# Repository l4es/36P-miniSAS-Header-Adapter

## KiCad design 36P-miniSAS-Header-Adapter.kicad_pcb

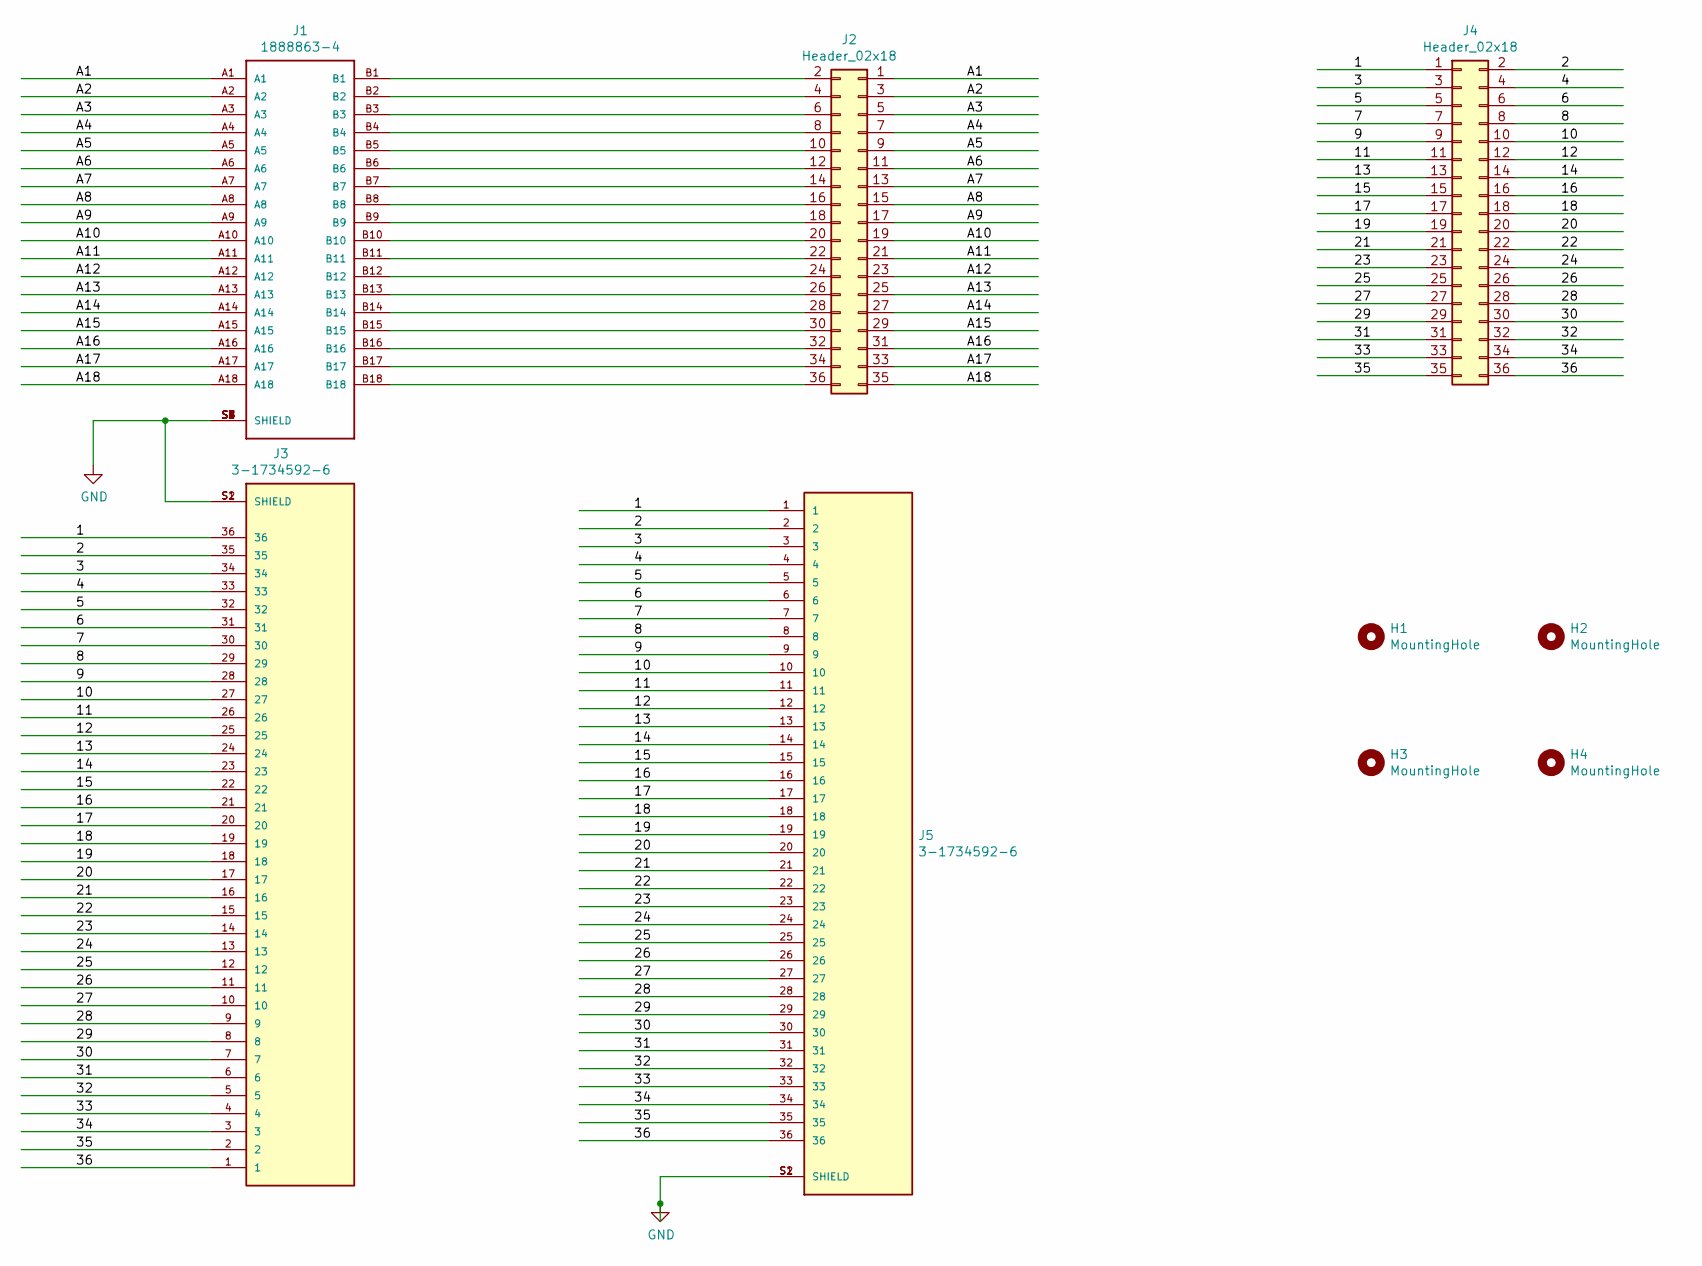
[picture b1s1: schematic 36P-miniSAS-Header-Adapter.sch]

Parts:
H1, H2, H3, H4: MountingHole; MountingHole_3.2mm_M3
J1: 1888863-4; TE_1888863-4
J2, J4: Header_02x18; PinHeader_2x18_P2.54mm_Vertical
J3, J5: 3-1734592-6; TE_3-1734592-6; PARTREV C

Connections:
/1: J3.36, J4.1, J5.1
/2: J3.35, J4.2, J5.2
/3: J3.34, J4.3, J5.3
/4: J3.33, J4.4, J5.4
/5: J3.32, J4.5, J5.5
/6: J3.31, J4.6, J5.6
/7: J3.30, J4.7, J5.7
/8: J3.29, J4.8, J5.8
/9: J3.28, J4.9, J5.9
/10: J3.27, J4.10, J5.10
/11: J3.26, J4.11, J5.11
/12: J3.25, J4.12, J5.12
/13: J3.24, J4.13, J5.13
/14: J3.23, J4.14, J5.14
/15: J3.22, J4.15, J5.15
/16: J3.21, J4.16, J5.16
/17: J3.20, J4.17, J5.17
/18: J3.19, J4.18, J5.18
/19: J3.18, J4.19, J5.19
/20: J3.17, J4.20, J5.20
/21: J3.16, J4.21, J5.21
/22: J3.15, J4.22, J5.22
/23: J3.14, J4.23, J5.23
/24: J3.13, J4.24, J5.24
/25: J3.12, J4.25, J5.25
/26: J3.11, J4.26, J5.26
/27: J3.10, J4.27, J5.27
/28: J3.9, J4.28, J5.28
/29: J3.8, J4.29, J5.29
/30: J3.7, J4.30, J5.30
/31: J3.6, J4.31, J5.31
/32: J3.5, J4.32, J5.32
/33: J3.4, J4.33, J5.33
/34: J3.3, J4.34, J5.34
/35: J3.2, J4.35, J5.35
/36: J3.1, J4.36, J5.36
/A1: J1.A1, J2.1
/A2: J1.A2, J2.3
/A3: J1.A3, J2.5
/A4: J1.A4, J2.7
/A5: J1.A5, J2.9
/A6: J1.A6, J2.11
/A7: J1.A7, J2.13
/A8: J1.A8, J2.15
/A9: J1.A9, J2.17
/A10: J1.A10, J2.19
/A11: J1.A11, J2.21
/A12: J1.A12, J2.23
/A13: J1.A13, J2.25
/A14: J1.A14, J2.27
/A15: J1.A15, J2.29
/A16: J1.A16, J2.31
/A17: J1.A17, J2.33
/A18: J1.A18, J2.35
GND: J1.S1 (SHIELD), J1.S2 (SHIELD), J1.S3 (SHIELD), J1.S4 (SHIELD), J1.S5 (SHIELD), J1.S6 (SHIELD), J1.S7 (SHIELD), J1.S8 (SHIELD), J3.S1 (SHIELD), J3.S2 (SHIELD), J5.S1 (SHIELD), J5.S2 (SHIELD)
unnamed: J1.B1, J2.2
unnamed: J1.B2, J2.4
unnamed: J1.B3, J2.6
unnamed: J1.B4, J2.8
unnamed: J1.B5, J2.10
unnamed: J1.B6, J2.12
unnamed: J1.B7, J2.14
unnamed: J1.B8, J2.16
unnamed: J1.B9, J2.18
unnamed: J1.B10, J2.20
unnamed: J1.B11, J2.22
unnamed: J1.B12, J2.24
unnamed: J1.B13, J2.26
unnamed: J1.B14, J2.28
unnamed: J1.B15, J2.30
unnamed: J1.B16, J2.32
unnamed: J1.B17, J2.34
unnamed: J1.B18, J2.36

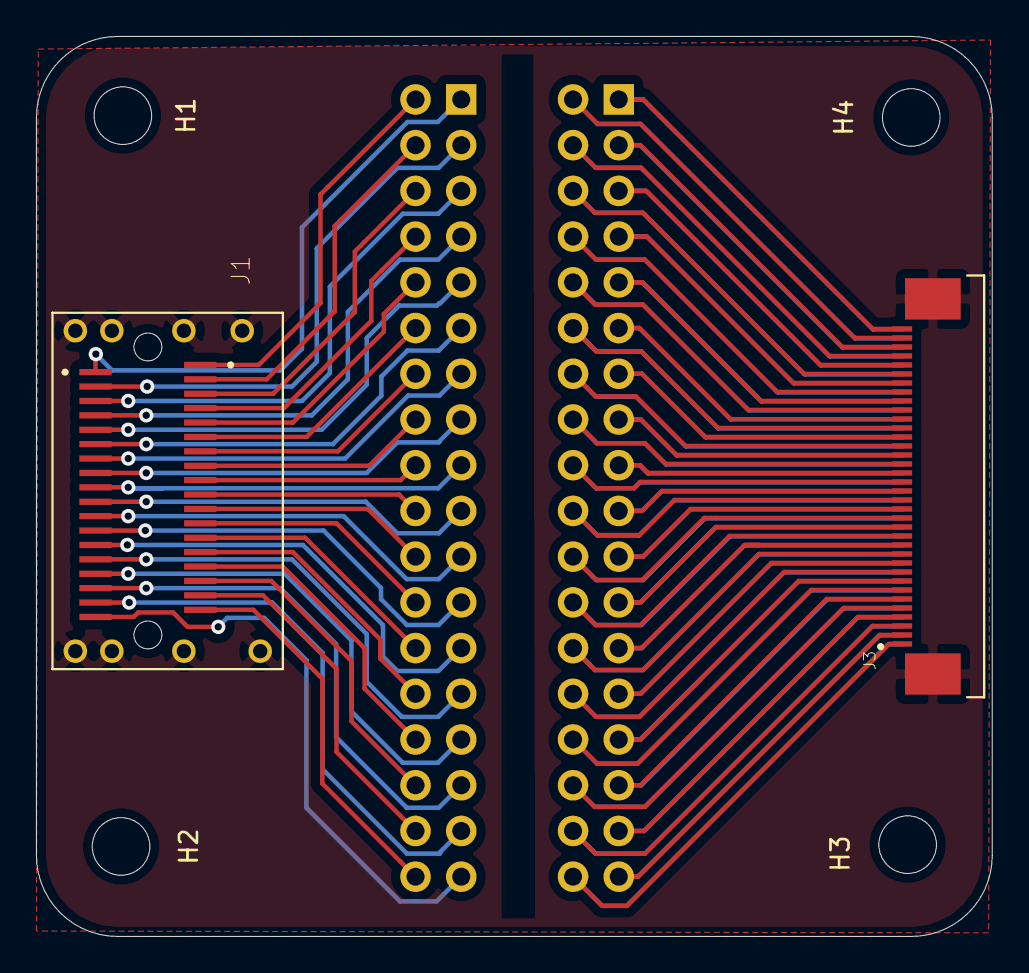
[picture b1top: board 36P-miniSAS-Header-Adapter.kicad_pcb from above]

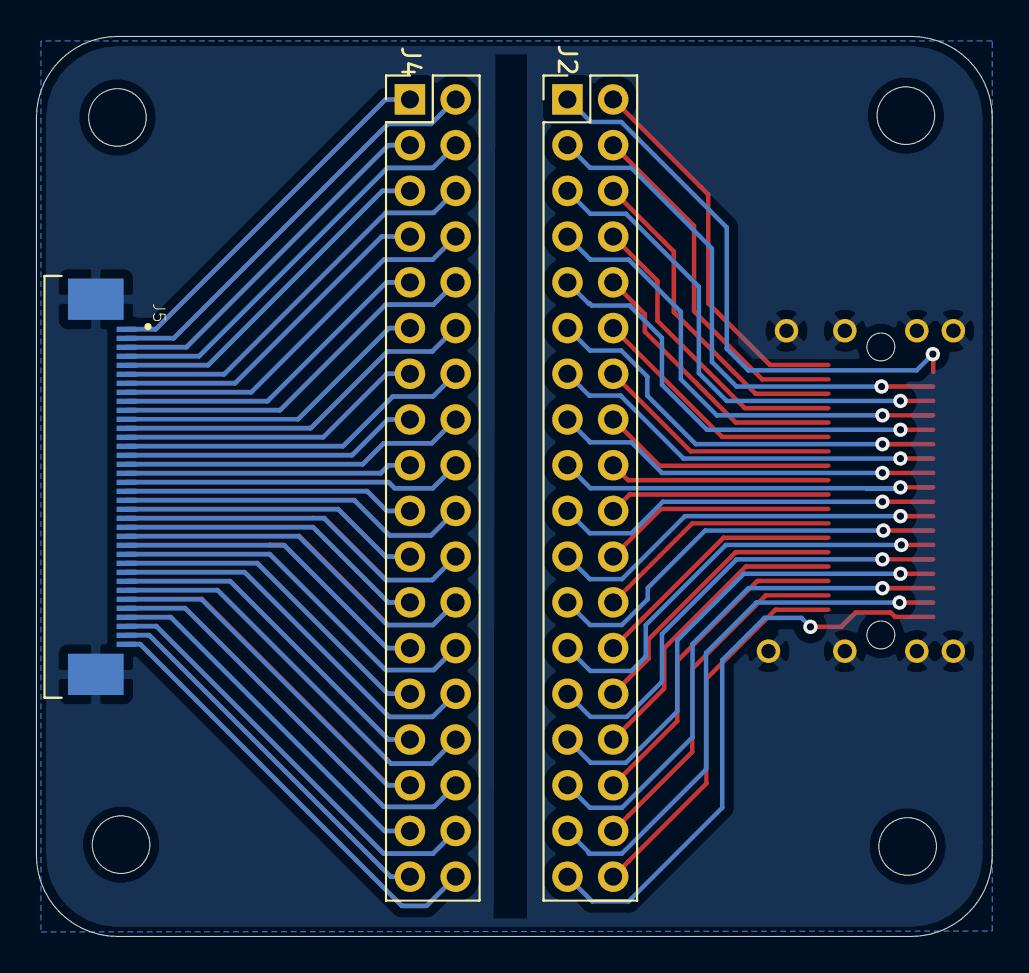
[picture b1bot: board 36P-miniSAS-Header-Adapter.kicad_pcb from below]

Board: 2 copper layers, 53.1 x 50.0 mm, 9 parts (3 on the bottom side), 73 nets.

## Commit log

2021-05-23 Add library submodules
2021-05-23 Add specific symbols & footprints used in the project
2021-05-23 Draw schematic
2021-05-24 Add layout drawing
2021-05-24 Finalize pcb routing
2021-05-25 Add round corners
2021-05-25 Refill copper zones
2021-05-25 Add gerbers V1A
2022-06-15 Add PDF schematic for V1A
